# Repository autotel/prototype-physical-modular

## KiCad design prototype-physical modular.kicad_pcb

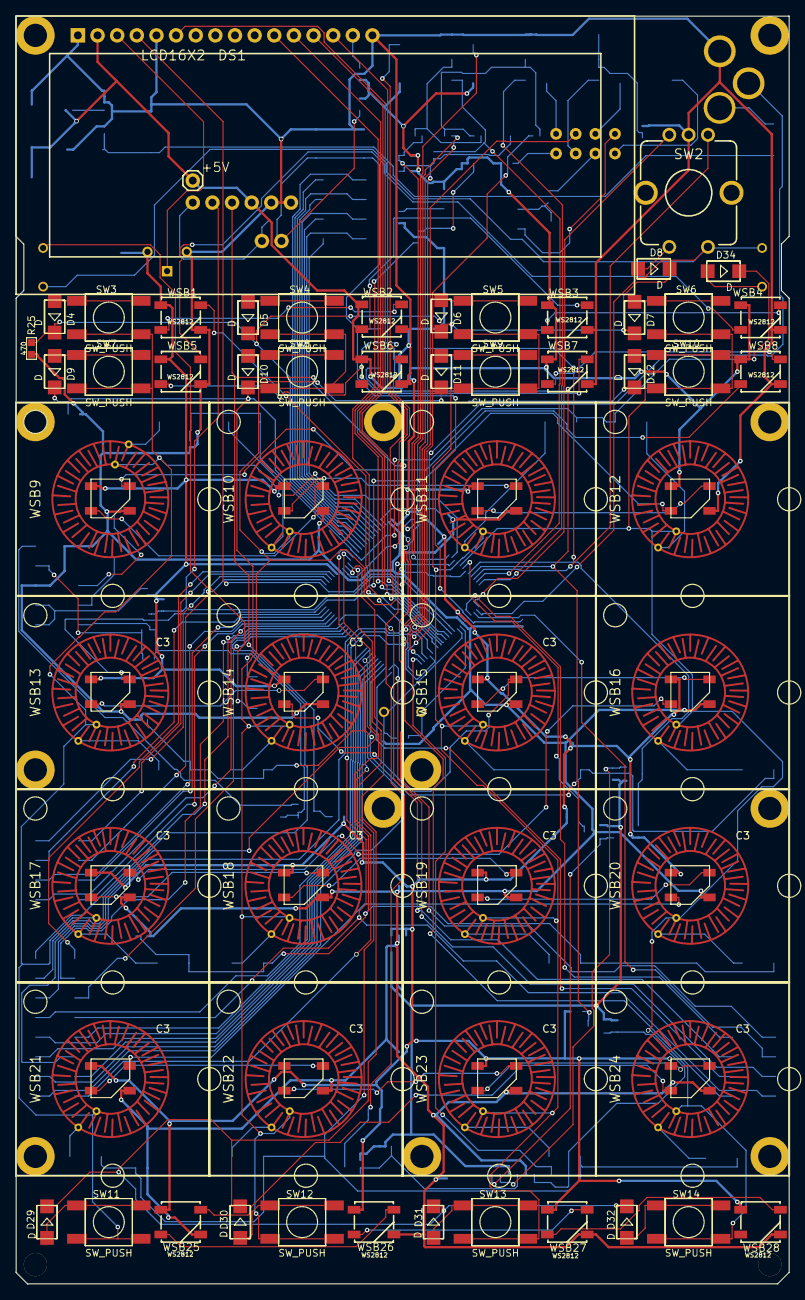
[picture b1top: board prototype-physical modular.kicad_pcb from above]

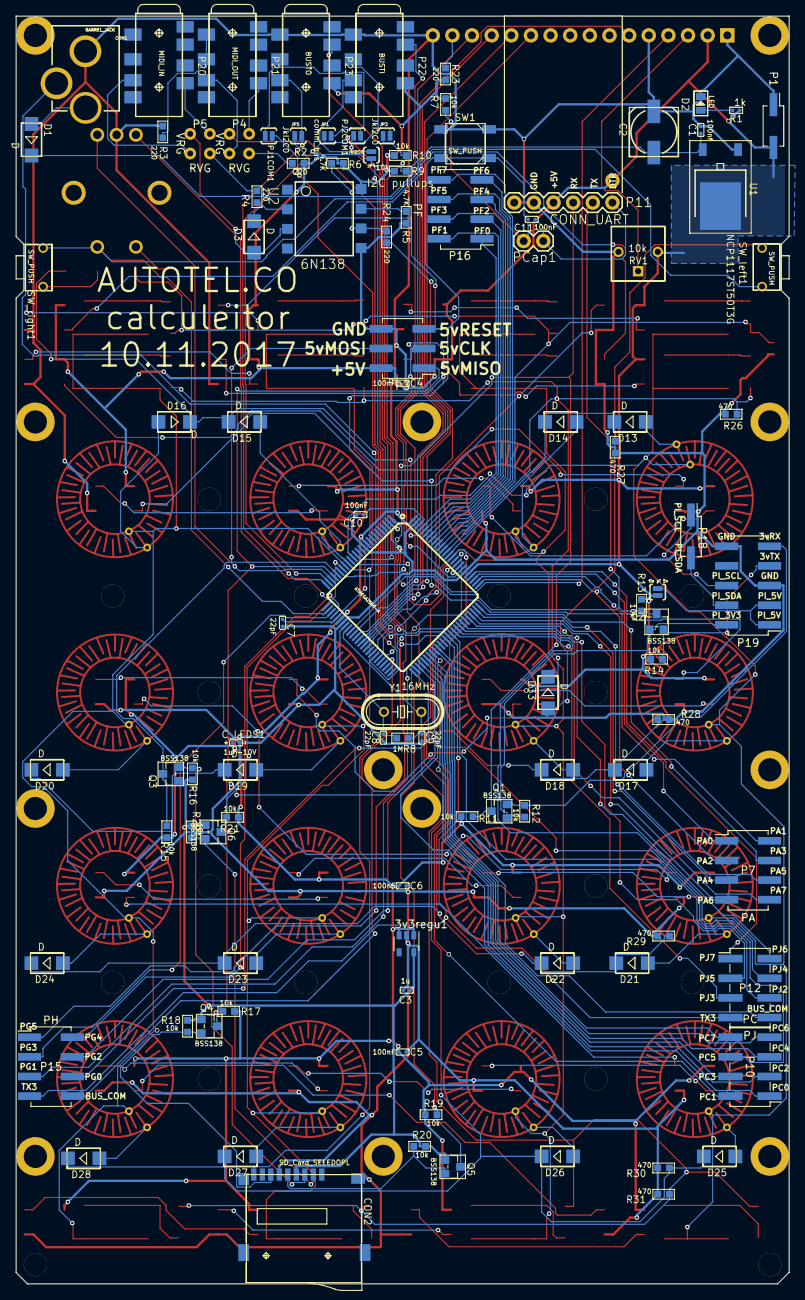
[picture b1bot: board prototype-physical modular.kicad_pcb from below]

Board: 2 copper layers, 100.0 x 164.0 mm, 188 parts (103 on the bottom side), 168 nets.

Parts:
3v3regu1: TLV70233DBV; SOT-23-5
+5V: >VALUE; 1X01
C1: 100nf; C0402
C2: Aluminum 47uF-25V; ELECTRO-SMD-C-6MM
C3: 1u; C0402
C4, C5, C6, C10, C11: 100nF; C0402
C7, C8, C9: 22pF; C0402
CON1: BARREL_JACK; POWER_JACK_PTH_LOCK
CON2: SD_Card_SEEEDOPL; MICRO-SD9+4P-SMD-16.1X14.5X1.85MM
C_LEDS1: 1uF-10V; C0402_electrolitic
D1, D3, D4, D5, D6, D7, D8, D9, D10, D11, D12, D13, D14, D15, D16, D17, D18, D19, D20, D21, D22, D23, D24, D25, D26, D27, D28, D29, D30, D31, D32, D33, D34: D; DO-214AC
D2: LED; LED-0805
DS1: LCD16X2; LCD-16X2
H1, H2, H3, H4, H5, H6, H7, H8, H9, H10, H11, H12, H26, H27, H28, H29, H30: hole; hole_no-copper
H13, H14, H15, H16, H18, H20, H21, H22, H23, H24: hole; hole_with-copper
IC1: ATMEGA2560-A; TQFP100
JP1: comm_bus; PAD-JUMPER-2-NO_YES_SILK
JP2: tie pi 5v; PAD-JUMPER-2-NO_YES_SILK
JP3, JP4, JP5: JkI2C0; PAD-JUMPER-2-NO_YES_SILK
P1: POWER; Pin_Header_Straight_2x01_Pitch2.54mm_SMD
P3: SPI; Pin_Header_Straight_2x03_Pitch2.54mm_SMD
P4, P5: CONN_02X02; xjump
P7: PA; Pin_Header_Straight_2x04_Pitch2.54mm_SMD
P10: PC; Pin_Header_Straight_2x04_Pitch2.54mm_SMD
P11: CONN_UART; 1X06
P12: PJ; Pin_Header_Straight_2x04_Pitch2.54mm_SMD
P15: PH; Pin_Header_Straight_2x04_Pitch2.54mm_SMD
P16: PF; Pin_Header_Straight_2x04_Pitch2.54mm_SMD
P18: 3VI2C; Pin_Header_Straight_2x01_Pitch2.54mm_SMD
P19: PIGPIO; Pin_Header_Straight_2x05_Pitch2.54mm_SMD-raspi
P20: MIDI_IN; AUDIO8P-SMD-3.5-14.5X6.1X4.0MM
P21: MIDI_OUT; AUDIO8P-SMD-3.5-14.5X6.1X4.0MM
P22: BUSTI; AUDIO8P-SMD-3.5-14.5X6.1X4.0MM
P23: BUSTO; AUDIO8P-SMD-3.5-14.5X6.1X4.0MM
PCap1: CONN_01X02; 1X02
PJ1COM1, PJ2COM1: Jumper_NO_Small; PAD-JUMPER-2-NO_YES_SILK
Q1, Q2, Q3, Q4, Q5, Q6: BSS138; SOT-23
R1: 1k; R0402
R2, R3, R4, R23, R24: 220; R0603
R5, R6: 4.7K; R0603
R7, R9, R10, R11, R12, R13, R14, R15, R16, R17, R18, R19, R20, R21, R22: 10k; R0603
R8: 1M; R0603
R25, R26, R27, R28, R29, R30, R31: 470; R0603
RV1: 10k; trimpot
SW1: SW_PUSH; SW4-SMD-5.2X5.2X1.5MM
SW2: ROTARY_ENCODER_SWITCH; ENCODER_LED_2
SW3, SW4, SW5, SW6, SW7, SW8, SW9, SW10, SW11, SW12, SW13, SW14: SW_PUSH; SW4-SMD-6.0X6.0X5.0MM
SW_left1: SW_PUSH; SW2-5.0-6.0X3.0X4.3MM
SW_right1: SW_PUSH; SW2-5.0-6.0X3.0X4.3MM
U1: NCP1117ST50T3G; TO-252
U2: 6N138; 8-SMD
WSB1, WSB2, WSB3, WSB4, WSB5, WSB6, WSB7, WSB8, WSB25, WSB26, WSB27, WSB28: WS2812; WS2812B
WSB9, WSB10, WSB11, WSB12, WSB13, WSB14, WSB15, WSB16, WSB17, WSB18, WSB19, WSB20, WSB21, WSB22, WSB23, WSB24: WS2812_BUTTON; ws2812_buttonPad
Y1: 16MHz; HC49US

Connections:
+3V3: 3v3regu1.5, C3.1, CON2.4, Q3.1, Q4.1, Q5.1, Q6.1, R16.1, R18.1, R20.1, R22.1
+5V: 3v3regu1.1, 3v3regu1.3, +5V.1, C4.1, C5.1, C6.1, C_LEDS1.1, DS1.2, IC1.10, IC1.31, IC1.80, IC1.100, JP2.2, P1.2, P3.2, P11.3, P22.4, P23.4, R1.1, R2.1, R6.2, R7.1, R9.1, R10.1, R11.2, R13.2, R15.2, R17.2, R19.2, R21.2, R23.1, RV1.1, U1.2, U2.8, WSB1.1, WSB2.1, WSB3.1, WSB4.1, WSB5.1, WSB6.1, WSB7.1, WSB8.1, WSB9.1, WSB10.1, WSB11.1, WSB12.1, WSB13.1, WSB14.1, WSB15.1, WSB16.1, WSB17.1, WSB18.1, WSB19.1, WSB20.1, WSB21.1, WSB22.1, WSB23.1, WSB24.1, WSB25.1, WSB26.1, WSB27.1, WSB28.1
/3VSD_CS: CON2.2, Q6.2, R22.2
/3vRX0: P19.9, Q1.2, R12.2
/3vSPI_MISO: CON2.7, Q4.2, R18.2
/3vSPI_MOSI: CON2.3, Q3.2, R16.2
/3vSPI_SCK: CON2.5, Q5.2, R20.2
/3vTX0: P19.7, Q2.2, R14.2
/5VSD_CLK: IC1.20, P3.3, Q5.3, R19.1
/5VSD_CS: IC1.19, Q6.3, R21.1
/5VSD_MISO: IC1.22, P3.1, Q4.3, R17.1
/5VSD_MOSI: IC1.21, P3.4, Q3.3, R15.1
/BUSTI_CONN: IC1.82, P22.6
/BUSTO_CONN: IC1.14, P23.6
/BUS_COM: IC1.63, JP1.1, JP3.2, P12.8, P15.8, P22.2
/BUS_COM_B: JP1.2, P23.2, PJ1COM1.1, PJ2COM1.1
/BUS_TI: IC1.24, JP4.2, P22.3
/BUS_TO: IC1.25, JP5.2, P23.3
/DTR: C11.1, P11.6, PCap1.2
/ENCA: IC1.23, SW2.A
/ENCC: IC1.26, SW2.B
/LCD0: DS1.4, IC1.35
/LCD1: DS1.6, IC1.36
/LCD2: DS1.11, IC1.37
/LCD3: DS1.12, IC1.38
/LCD4: DS1.13, IC1.39
/LCD5: DS1.14, IC1.40
/MIDI_IN_RX_PRE: D3.+, P5.3, U2.3
/MIDI_OUT_TX: IC1.46, P4.3
/MIDI_RX: IC1.45, R24.2
/MUXAX0: IC1.15, SW3.2, SW7.2, SW11.2, WSB9.6, WSB13.6, WSB17.6, WSB21.6
/MUXAX1: IC1.16, SW4.2, SW8.2, SW12.2, WSB10.6, WSB14.6, WSB18.6, WSB22.6
/MUXAX2: IC1.17, SW5.2, SW9.2, SW13.2, WSB11.6, WSB15.6, WSB19.6, WSB23.6
/MUXAX3: IC1.18, SW6.2, SW10.2, SW14.2, WSB12.6, WSB16.6, WSB20.6, WSB24.6
/MUXAX4: IC1.27, SW2.D, SW_left1.2, SW_right1.2
/MUXBX0: D4.-, D5.-, D6.-, D7.-, D8.-, IC1.89, R25.2
/MUXBX1: D9.-, D10.-, D11.-, D12.-, D33.-, IC1.88, R26.2
/MUXBX2: D13.-, D14.-, D15.-, D16.-, D34.-, IC1.87, R27.2
/MUXBX3: D17.-, D18.-, D19.-, D20.-, IC1.86, R28.2
/MUXBX4: D21.-, D22.-, D23.-, D24.-, IC1.85, R29.1
/MUXBX5: D25.-, D26.-, D27.-, D28.-, IC1.84, R30.1
/MUXBX6: D29.-, D30.-, D31.-, D32.-, IC1.83, R31.1
/PI5vRX0: IC1.2, P11.4, Q1.3, R11.1
/PI5vTX0: IC1.3, P11.5, Q2.3, R13.1
/PI_3V3: P19.2, Q1.1, Q2.1, R12.1, R14.1
/PI_5V: JP2.1, P19.1, P19.3
/PI_SCL: P18.1, P19.6
/PI_SDA: P18.2, P19.4
/POWER_IS: CON1.GNDB, IC1.50
/RESET: C7.1, C11.2, IC1.30, P3.5, PCap1.1, R7.2, SW1.2
/SCL: IC1.43, JP4.1, JP5.1, R9.2
/SDA: IC1.44, JP3.1, R10.2
/SD_CDetc: CON2.9, IC1.47
/SERIAL_LED_PIN: IC1.41, WSB1.4
/SERIAL_LED_TOROW_1: WSB4.2, WSB5.4
/SERIAL_LED_TOROW_2: WSB8.2, WSB9.4
/SERIAL_LED_TOROW_3: WSB12.2, WSB13.4
/SERIAL_LED_TOROW_4: WSB16.2, WSB17.4
/SERIAL_LED_TOROW_5: WSB20.2, WSB21.4
/SERIAL_LED_TOROW_6: WSB24.2, WSB25.4
/TX3: IC1.64, P12.7, P15.7, PJ1COM1.2
GND: 3v3regu1.2, C1.2, C2.+, C3.2, C4.2, C5.2, C6.2, C7.2, C8.2, C9.2, C10.2, CON1.GND, CON2.6, CON2.G4, C_LEDS1.2, D2.-, DS1.1, DS1.5, DS1.16, IC1.11, IC1.32, IC1.81, IC1.99, P1.1, P3.6, P11.1, P11.2, P19.5, P19.10, P22.1, P23.1, R3.2, R5.1, R25.1, R26.1, R27.1, R28.1, R29.2, R30.2, R31.2, RV1.3, SW1.1, SW2.C, U1.1, U2.5, WSB1.3, WSB2.3, WSB3.3, WSB4.3, WSB5.3, WSB6.3, WSB7.3, WSB8.3, WSB9.3, WSB10.3, WSB11.3, WSB12.3, WSB13.3, WSB14.3, WSB15.3, WSB16.3, WSB17.3, WSB18.3, WSB19.3, WSB20.3, WSB21.3, WSB22.3, WSB23.3, WSB24.3, WSB25.3, WSB26.3, WSB27.3, WSB28.3
unnamed: C1.1, C2.-, D1.-, U1.3
unnamed: C8.1, IC1.33, R8.1, Y1.1
unnamed: C9.1, IC1.34, R8.2, Y1.2
unnamed: C10.1, IC1.98
unnamed: CON1.PWR, D1.+
unnamed: D2.+, R1.2
unnamed: D3.-, R4.2, U2.2
unnamed: D4.+, SW3.1
unnamed: D5.+, SW4.1
unnamed: D6.+, SW5.1
unnamed: D7.+, SW6.1
unnamed: D8.+, SW2.E
unnamed: D9.+, SW7.1
unnamed: D10.+, SW8.1
unnamed: D11.+, SW9.1
unnamed: D12.+, SW10.1
unnamed: D13.+, WSB9.5
unnamed: D14.+, WSB10.5
unnamed: D15.+, WSB11.5
unnamed: D16.+, WSB12.5
unnamed: D17.+, WSB13.5
unnamed: D18.+, WSB14.5
unnamed: D19.+, WSB15.5
unnamed: D20.+, WSB16.5
unnamed: D21.+, WSB17.5
unnamed: D22.+, WSB18.5
unnamed: D23.+, WSB19.5
unnamed: D24.+, WSB20.5
unnamed: D25.+, WSB21.5
unnamed: D26.+, WSB22.5
unnamed: D27.+, WSB23.5
unnamed: D28.+, WSB24.5
unnamed: D29.+, SW11.1
unnamed: D30.+, SW12.1
unnamed: D31.+, SW13.1
unnamed: D32.+, SW14.1
unnamed: D33.+, SW_left1.1
unnamed: D34.+, SW_right1.1
unnamed: DS1.3, RV1.2
unnamed: DS1.15, R23.2
unnamed: IC1.1, P15.1
unnamed: IC1.28, P15.3
unnamed: IC1.29, P15.2
unnamed: IC1.51, P15.6
unnamed: IC1.52, P15.5
unnamed: IC1.53, P10.1
unnamed: IC1.54, P10.2
unnamed: IC1.55, P10.3
unnamed: IC1.56, P10.4
unnamed: IC1.57, P10.5
unnamed: IC1.58, P10.6
unnamed: IC1.59, P10.7
unnamed: IC1.60, P10.8
unnamed: IC1.65, P12.6, PJ2COM1.2
unnamed: IC1.66, P12.5
unnamed: IC1.67, P12.4
unnamed: IC1.68, P12.3
unnamed: IC1.69, P12.2
unnamed: IC1.70, P15.4
unnamed: IC1.71, P7.8
unnamed: IC1.72, P7.7
unnamed: IC1.73, P7.6
unnamed: IC1.74, P7.5
unnamed: IC1.75, P7.4
unnamed: IC1.76, P7.3
unnamed: IC1.77, P7.2
unnamed: IC1.78, P7.1
unnamed: IC1.79, P12.1
unnamed: IC1.90, P16.8
unnamed: IC1.91, P16.7
unnamed: IC1.92, P16.6
unnamed: IC1.93, P16.5
unnamed: IC1.94, P16.4
unnamed: IC1.95, P16.3
unnamed: IC1.96, P16.2
unnamed: IC1.97, P16.1
unnamed: P4.2, R2.2
unnamed: P5.2, R4.1
unnamed: P5.4, P20.3
unnamed: P5.1, P20.4
unnamed: P21.1, P21.2, R3.1
unnamed: P4.4, P21.3
unnamed: P4.1, P21.4
unnamed: R5.2, U2.7
unnamed: R6.1, R24.1, U2.6
unnamed: WSB1.2, WSB2.4
unnamed: WSB2.2, WSB3.4
unnamed: WSB3.2, WSB4.4
unnamed: WSB5.2, WSB6.4
unnamed: WSB6.2, WSB7.4
unnamed: WSB7.2, WSB8.4
unnamed: WSB10.2, WSB11.4
unnamed: WSB9.2, WSB10.4
unnamed: WSB11.2, WSB12.4
unnamed: WSB13.2, WSB14.4
unnamed: WSB14.2, WSB15.4
unnamed: WSB15.2, WSB16.4
unnamed: WSB17.2, WSB18.4
unnamed: WSB18.2, WSB19.4
unnamed: WSB19.2, WSB20.4
unnamed: WSB21.2, WSB22.4
unnamed: WSB22.2, WSB23.4
unnamed: WSB23.2, WSB24.4
unnamed: WSB25.2, WSB26.4
unnamed: WSB26.2, WSB27.4
unnamed: WSB27.2, WSB28.4

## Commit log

2017-06-20 communication test firmwares and bare minimum atmega 2560 kicad shcematic
2017-06-20 forward with schematic added buttons, power, arduino pro mini interface, communication and midi interconnectors, screen & encoder
2017-06-21 schematic finished, subject to revisons added sd card, diodes in matrix, 3v3 voltage, modular headers fo Mega. test of button matrix that revealed need for diodes
2017-06-21 localize search for schematic component libraries
2017-06-21 assign seeedstudio parts sku and footprints where available
2017-06-22 made footprints for ws2812's with button replaced schematic symbols for the buttons that use tacht switches
2017-06-22 fill components metadata
2017-06-22 solving errors, placing elements in pcb
2017-06-22 fix more mistakes, forward with pcblayout
2017-06-22 fix more errors, advance more in pcb layout
2017-06-23 fix one connection mistake, forward trying to route pcb
2017-06-23 fixed diode footprints were wrong polarity. forward with routing
2017-06-23 MUXACOM not necessary
2017-06-23 netlist was being saved on wrong name
2017-06-23 still trying to make it routable
2017-06-26 -fix mistakes -fix wrong tact switches autorouter and manual router
2017-06-26 managed to autoroute
2017-06-27 corrected optocoupler connections, sorted labels, optimization of placement
2017-06-28 pot had wrong pins forward with pcb design
2017-06-28 create bom while routing
2017-06-28 Add I2C enabling Jumpers testing and beefing up TBN communication different arrangement try in PCB
2017-07-04 - testing communications with all the rest of the hardware - spotted wrongly connected CS pin for SD card
2017-07-07 remap pins in prototype tests, and changed TIP and TOP pins in schematic
2017-07-16 correction of BOM and routing
2017-09-11 correct wrong part number in midi inputs & outputs
2017-09-11 update gerbers
2017-09-25 annotation of some mistakes in board
2017-09-27 try measuring buttons with inverted register roles (are diodes the wrong way?)
2017-09-27 tested with inverted roles it works, but there is an obvious need for pullup or pulldown, all non pressed buttons are erratic
2017-09-27 figured out the buttons algorhythm
2017-09-27 analog read of the buttons. quite bad on this hardware configuration
2017-09-27 digital read not working?
2017-10-02 started working on minimum sequencer
2017-10-10 create firmware that would run in my node virtual modular interface. It has some memory leak note about the encoder in schematic for next production
2017-10-12 slower baud rate more stability in v2 finetuning and general mingling about firmware
2017-10-20 two: connect encoder and remove arduino pro mini in schematic controllerfirmware: improve encoder steps counting
2017-10-20 test and add pulldowns for buttons
2017-10-20 use lower resistor pulldown
2017-10-20 flip bus with +5V pins in the BUSTO &BUSTI plugs otherwise, it does a shortcircuit sometimes when plugging the jack in.
2017-10-20 reflect schematic changes on board
2017-10-20 button matrix diodes needed to be inverse
2017-10-21 fix sd card pins were catastrophically wrong still figuring out layout
2017-10-21 more layout, inclusion of enclosure design
2017-10-21 fix wrong midi jack plug
2017-10-21 fix the swap of bus jacks that was done wrong
2017-10-23 change name of CD sd
2017-10-24 sketch of midi implementation. not working well yet
2017-10-26 finetune of refresh rates in vm-controller mode
2017-10-31 correction of buttonmap
2017-11-02 flip FTDI to correct side, draw size fro better fit with enclosure & many others
2017-11-08 select better tact switches, add holes in the schematic to avoid future problems
2017-11-08 last commit
2017-11-08 modularized development of physical modules created object based scheme for multiple interaction patterns using the same structure
2017-11-09 firmware proper midi reception
2017-11-09 routed
2017-11-09 moved a couple of components around, updating the routing
2017-11-10 optimize design rules, location of some components, added labels to every connector pin
2017-11-12 creating firmware for x28 that is hybrid between standalone and controller. Setting up communication
2017-11-12 new go at routing
2017-11-12 move controller and hybrid firmware to virtualModular project
2017-11-17 job files for pcb assembly
2017-11-17 add slot for capacitor in case reset doesn't work
2017-11-17 proposal for standard/korg jumper in midi terminals
2017-11-17 manual route effort that will not be used
2018-03-19 enclosure changes and new prints. Unknown changes
